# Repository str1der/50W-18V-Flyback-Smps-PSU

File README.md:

# 50W 18V Smps Power Supply

Bir Smps Trafo tasarımı ile ilgili tüm hesaplama ve detaylar "./Documents/SMPS Documents.pdf" dosyasında mevcuttur. 

https://github.com/str1der/50W-18V-Smps-PSU/blob/main/BOM/BOM.csv

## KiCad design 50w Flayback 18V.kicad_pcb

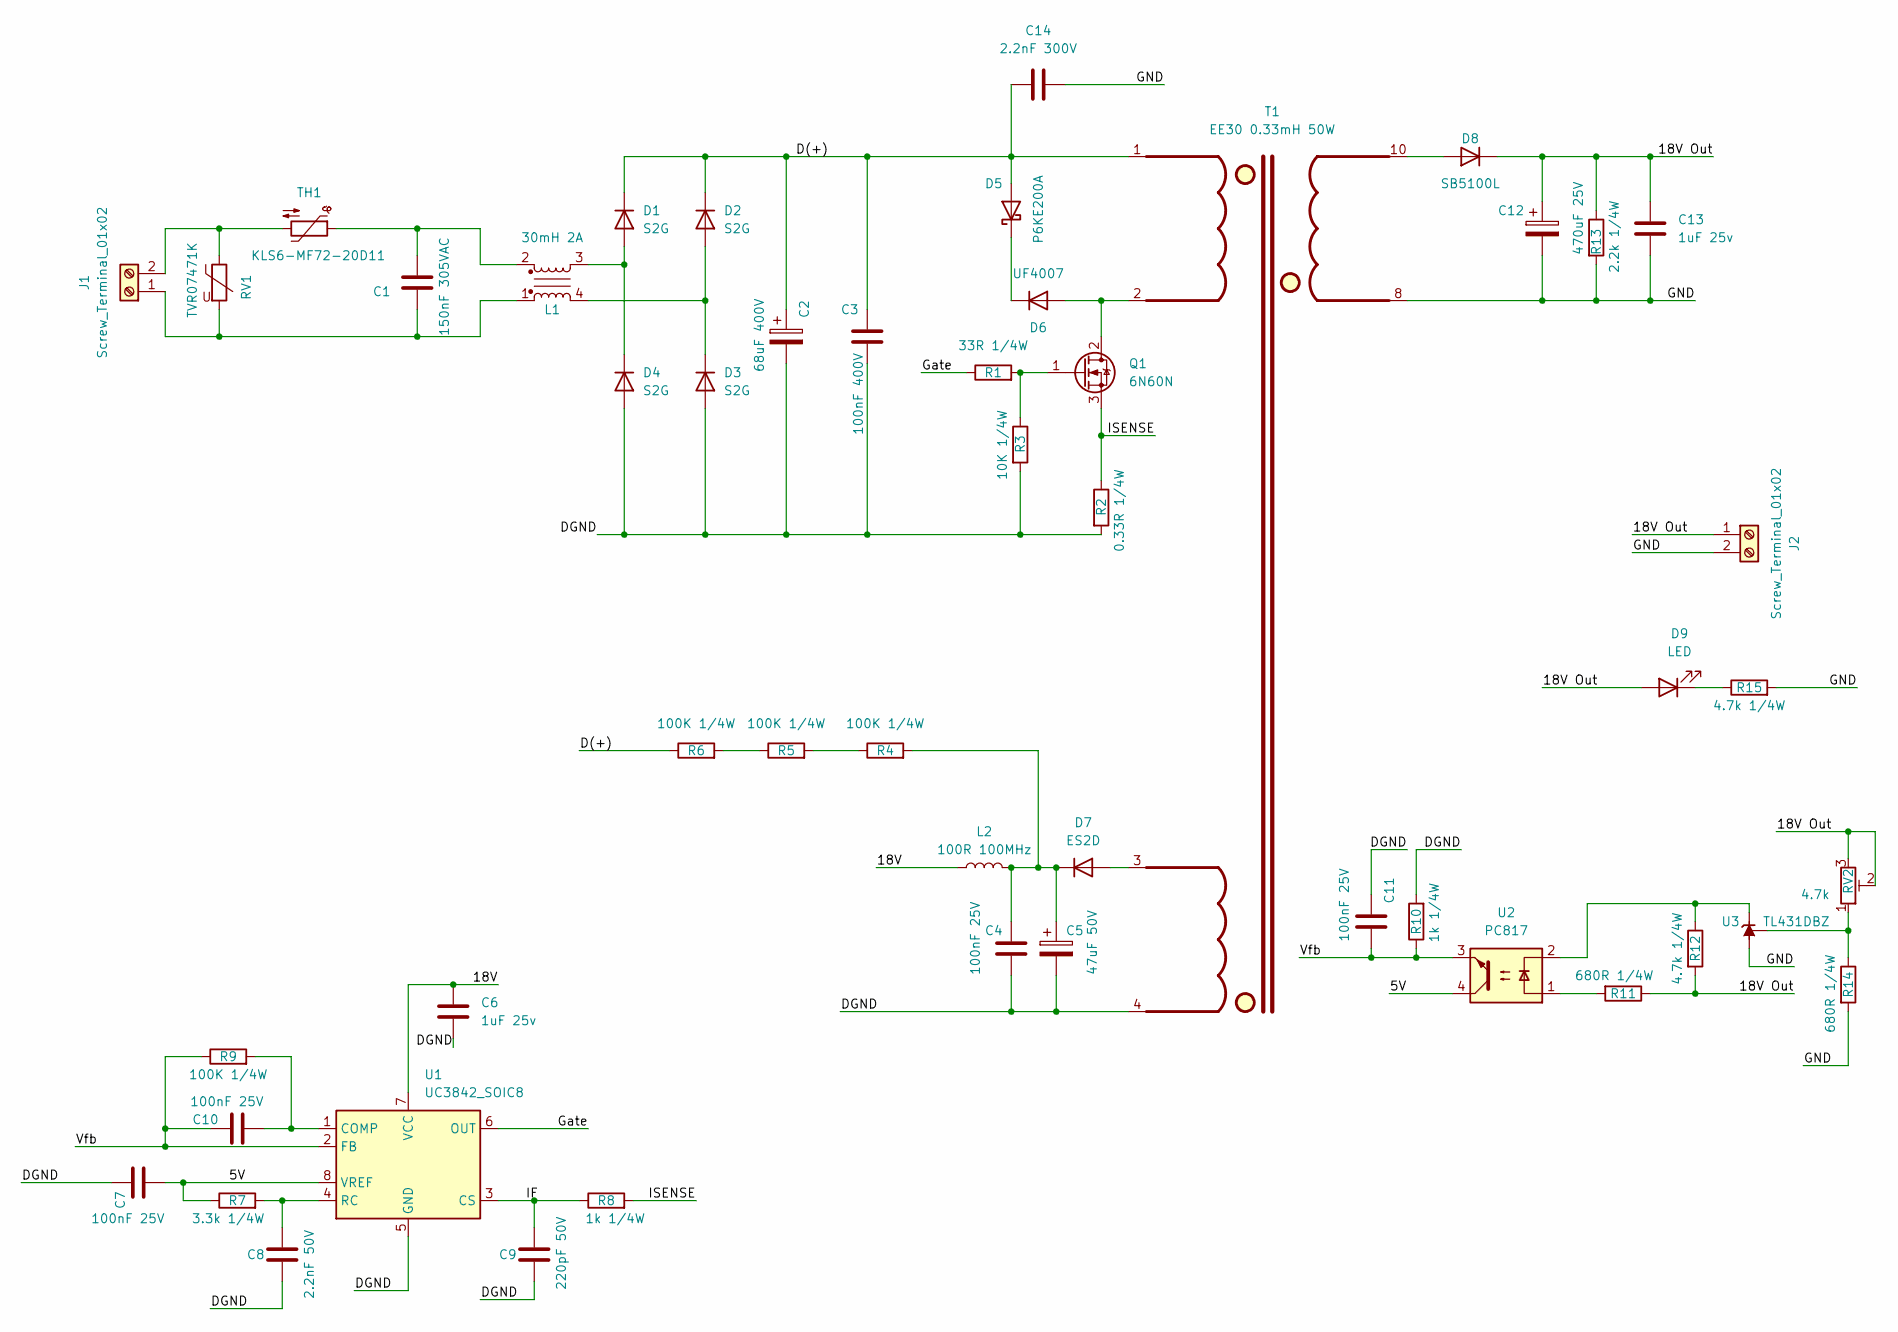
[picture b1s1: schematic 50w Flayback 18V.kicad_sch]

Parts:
C1: 150nF 305VAC; C_Rect_L16.5mm_W6.0mm_P15.00mm_MKT
C2: 68uF 400V; CP_Radial_D18.0mm_P7.50mm
C3: 100nF 400V; C_Rect_L16.5mm_W4.7mm_P15.00mm_MKT
C4, C7, C10, C11: 100nF 25V; C_0805_2012Metric
C5: 47uF 50V; CP_Radial_D5.0mm_P2.50mm
C6, C13: 1uF 25v; C_0805_2012Metric
C8: 2.2nF 50V; C_0805_2012Metric
C9: 220pF 50V; C_0805_2012Metric
C12: 470uF 25V; CP_Radial_D8.0mm_P5.00mm
C14: 2.2nF 300V; C_Rect_L13.0mm_W4.0mm_P10.00mm_FKS3_FKP3_MKS4
D1, D2, D3, D4: S2G; D_SMB
D5: P6KE200A; D_DO-15_P3.81mm_Vertical_AnodeUp
D6: UF4007; D_DO-41_SOD81_P3.81mm_Vertical_AnodeUp
D7: ES2D; D_SMB
D8: SB5100L; D_DO-27_P12.70mm_Horizontal
D9: LED; D_0603_1608Metric
J1, J2: Screw_Terminal_01x02; Wago_734-132_1x02_P3.50mm_Vertical
L1: 30mH 2A; UU10.5
L2: 100R 100MHz; L_1206_3216Metric
Q1: 6N60N; TO-220-3_Vertical
R1: 33R 1/4W; R_1206_3216Metric
R2: 0.33R 1/4W; R_Axial_DIN0204_L3.6mm_D1.6mm_P2.54mm_Vertical
R3: 10K 1/4W; R_1206_3216Metric
R4, R5, R6, R9: 100K 1/4W; R_1206_3216Metric
R7: 3.3k 1/4W; R_1206_3216Metric
R8, R10: 1k 1/4W; R_1206_3216Metric
R11, R14: 680R 1/4W; R_1206_3216Metric
R12, R15: 4.7k 1/4W; R_1206_3216Metric
R13: 2.2k 1/4W; R_1206_3216Metric
RV1: TVR07471K; RV_Disc_D9mm_W6.1mm_P5mm
RV2: 4.7k; Potentiometer_Bourns_3386F_Vertical
T1: EE30 0.33mH 50W; EE30-10pin
TH1: KLS6-MF72-20D11; RV_Disc_D12mm_W3.9mm_P7.5mm
U1: UC3842_SOIC8; SOIC-8_3.9x4.9mm_P1.27mm
U2: PC817; DIP-4_W7.62mm
U3: TL431DBZ; SOT-23

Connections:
/5V: C7.2, R7.1, U1.8 (VREF), U2.4
/18V: C6.1, L2.1, U1.7 (VCC)
/18V Out: C12.1, C13.1, D8.1 (K), D9.2 (A), J2.1, R11.1, R12.2, R13.1, RV2.2, RV2.3
/D(+): C2.1, C3.1, C14.1, D1.1 (K), D2.1 (K), D5.2 (A), R6.1, T1.1
/DGND: C2.2, C3.2, C4.2, C5.2, C6.2, C7.1, C8.2, C9.2, C11.2, D3.2 (A), D4.2 (A), R2.2, R3.2, R10.2, T1.4, U1.5 (GND)
/GND: C12.2, C13.2, C14.2, J2.2, R13.2, R14.2, R15.2, T1.8, U3.3 (A)
/Gate: R1.1, U1.6 (OUT)
/IF: C9.1, R8.1, U1.3 (CS)
/ISENSE: Q1.3 (S), R2.1, R8.2
/Vfb: C10.1, C11.1, R9.1, R10.1, U1.2 (FB), U2.3
unnamed: C1.1, L1.2, TH1.1
unnamed: D1.2 (A), D4.1 (K), L1.3
unnamed: D2.2 (A), D3.1 (K), L1.4
unnamed: D5.1 (K), D6.1 (K)
unnamed: D6.2 (A), Q1.2 (D), T1.2
unnamed: D7.2 (A), T1.3
unnamed: C4.1, C5.1, D7.1 (K), L2.2, R4.2
unnamed: D8.2 (A), T1.10
unnamed: D9.1 (K), R15.1
unnamed: C1.2, J1.1, L1.1, RV1.2
unnamed: J1.2, RV1.1, TH1.2
unnamed: Q1.1 (G), R1.2, R3.1
unnamed: R4.1, R5.2
unnamed: R5.1, R6.2
unnamed: R11.2, U2.1
unnamed: C10.2, R9.2, U1.1 (COMP)
unnamed: C8.1, R7.2, U1.4 (RC)
unnamed: R12.1, U2.2, U3.1 (K)
unnamed: R14.1, RV2.1, U3.2 (REF)

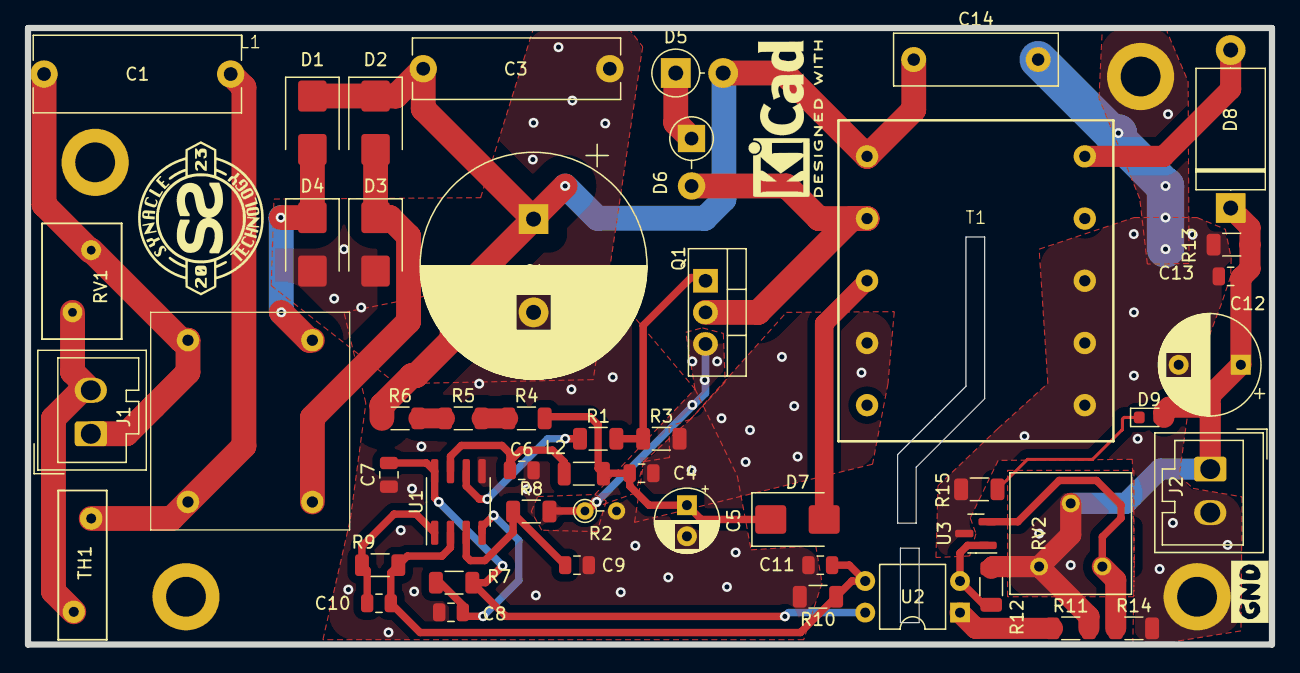
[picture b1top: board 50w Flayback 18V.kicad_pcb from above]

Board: 2 copper layers, 100.0 x 49.6 mm, 50 parts (0 on the bottom side), 29 nets.

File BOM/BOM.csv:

"Reference","Value","Footprint","Datasheet","Sim.Device","Sim.Library","Sim.Name","Sim.Params","Sim.Pins","Qty"
"C1","150nF 305VAC","Capacitor_THT:C_Rect_L16.5mm_W6.0mm_P15.00mm_MKT","~","","","","","","1"
"C2","68uF 400V","Capacitor_THT:CP_Radial_D18.0mm_P7.50mm","~","","","","","","1"
"C3","100nF 400V","Capacitor_THT:C_Rect_L9.0mm_W3.2mm_P7.50mm_MKT","~","","","","","","1"
"C4, C7, C10, C11","100nF 25V","Capacitor_SMD:C_0805_2012Metric","~","","","","","","4"
"C5","47uF 50V","Capacitor_THT:CP_Radial_D8.0mm_P5.00mm","~","","","","","","1"
"C6, C13","1uF 25v","Capacitor_SMD:C_0805_2012Metric","~","","","","","","2"
"C8","2.2nF 50V","Capacitor_SMD:C_1206_3216Metric","~","","","","","","1"
"C9","220pF 50V","Capacitor_SMD:C_1206_3216Metric","~","","","","","","1"
"C12","450uF 25V","Capacitor_THT:CP_Radial_D8.0mm_P5.00mm","~","","","","","","1"
"D1-D4","S2G","Diode_SMD:D_SMB","https://www.onsemi.com/pub/Collateral/US2AA-D.PDF","D","","","","1=K 2=A","4"
"D5","P6KE200A","Diode_THT:D_DO-15_P3.81mm_Vertical_AnodeUp","~","","","","","","1"
"D6","UF4007","Diode_THT:D_DO-41_SOD81_P3.81mm_Vertical_AnodeUp","~","D","","","","1=K 2=A","1"
"D7","ES2D","Diode_SMD:D_SMB","~","D","","","","1=K 2=A","1"
"D8","SB5100L","Diode_THT:D_DO-27_P12.70mm_Horizontal","~","D","","","","1=K 2=A","1"
"J1, J2","Screw_Terminal_01x02","Connector_Wago:Wago_734-132_1x02_P3.50mm_Vertical","~","","","","","","2"
"L1","28mH 2A","Common_mode:SQ1515","http://www.meisongbei.com/res/meisongbei/pdres/202111/flat_w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","","","","","","1"
"L2","100R 100MHz","Inductor_SMD:L_1206_3216Metric","~","","","","","","1"
"Q1","6N60N","Package_TO_SOT_THT:TO-220-3_Vertical","https://pdf.direnc.net/upload/6n60-datasheet.pdf","","","","","","1"
"R1","33R 1/4W","Resistor_SMD:R_1206_3216Metric","~","","","","","","1"
"R2","0.33R 1/4W","Resistor_THT:R_Axial_DIN0204_L3.6mm_D1.6mm_P2.54mm_Vertical","~","","","","","","1"
"R3","10K 1/4W","Resistor_SMD:R_1206_3216Metric","~","","","","","","1"
"R4-R6, R9","100K 1/4W","Resistor_SMD:R_1206_3216Metric","~","","","","","","4"
"R7","3.3k 1/4W","Resistor_SMD:R_1206_3216Metric","~","","","","","","1"
"R8, R10","1k 1/4W","Resistor_SMD:R_1206_3216Metric","~","","","","","","2"
"R11, R14","680R 1/4W","Resistor_SMD:R_1206_3216Metric","~","","","","","","2"
"R12","4.7k 1/4W","Resistor_SMD:R_1206_3216Metric","~","","","","","","1"
"R13","2.2k 1/4W","Resistor_SMD:R_1206_3216Metric","~","","","","","","1"
"RV1","TVR07471K","Varistor:RV_Disc_D9mm_W6.1mm_P5mm","~","SUBCKT","${KICAD7_SYMBOL_DIR}/Simulation_SPICE.sp","kicad_builtin_varistor","threshold=1k","1=A 2=B","1"
"RV2","4.7k","Potentiometer_THT:Potentiometer_Bourns_3339W_Horizontal","~","","","","","","1"
"T1","EE30 0.33mH 50W","","","","","","","","1"
"TH1","KLS6-MF72-20D11","Varistor:RV_Disc_D12mm_W3.9mm_P7.5mm","~","","","","","","1"
"U1","UC3842_SOIC8","Package_SO:SOIC-8_3.9x4.9mm_P1.27mm","http://www.ti.com/lit/ds/symlink/uc3842.pdf","","","","","","1"
"U2","PC817","Package_DIP:DIP-4_W7.62mm","http://www.soselectronic.cz/a_info/resource/d/pc817.pdf","","","","","","1"
"U3","TL431","Package_TO_SOT_SMD:SOT-23-5","http://www.ti.com/lit/ds/symlink/tl431.pdf","","","","","","1"

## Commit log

2024-02-20 V1.0
